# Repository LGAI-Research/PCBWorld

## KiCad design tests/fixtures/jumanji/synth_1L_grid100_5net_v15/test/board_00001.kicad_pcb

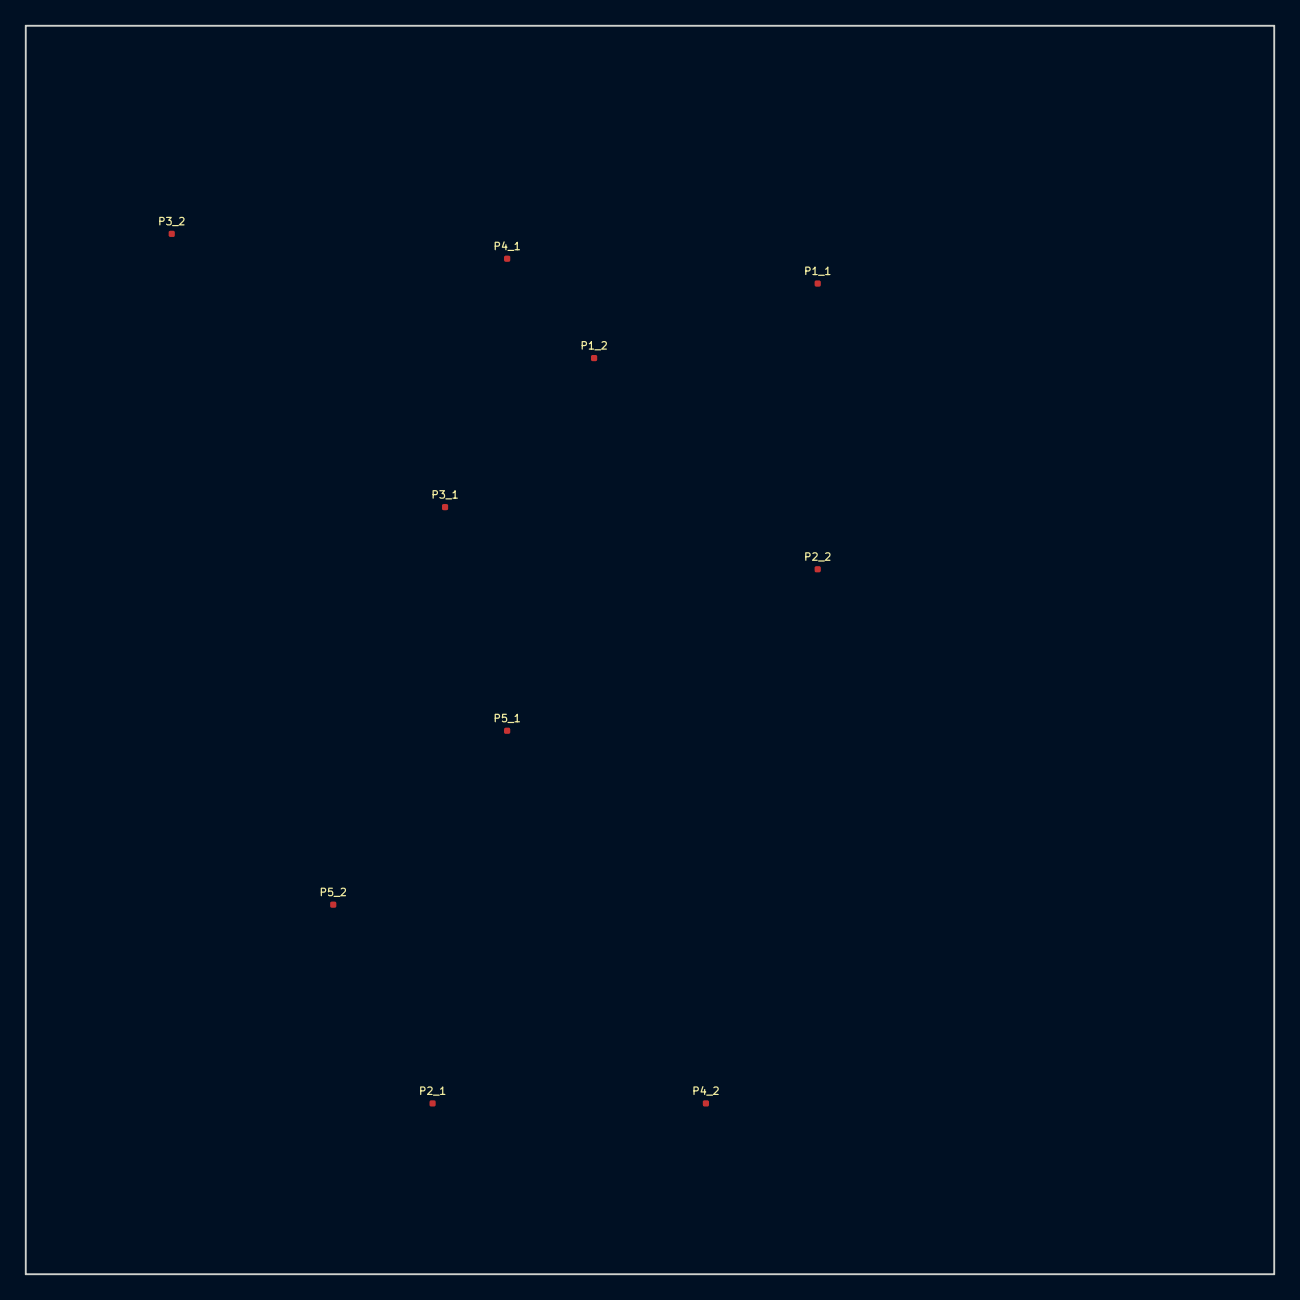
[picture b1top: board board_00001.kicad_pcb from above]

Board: 2 copper layers, 100.5 x 100.5 mm, 10 parts (0 on the bottom side), 5 nets, no tracks yet.

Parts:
P1_1, P2_1, P3_1, P4_1, P5_1: Pad1; FCu
P1_2, P2_2, P3_2, P4_2, P5_2: Pad2; FCu

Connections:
NET1: P1_1.1, P1_2.1
NET2: P2_1.1, P2_2.1
NET3: P3_1.1, P3_2.1
NET4: P4_1.1, P4_2.1
NET5: P5_1.1, P5_2.1

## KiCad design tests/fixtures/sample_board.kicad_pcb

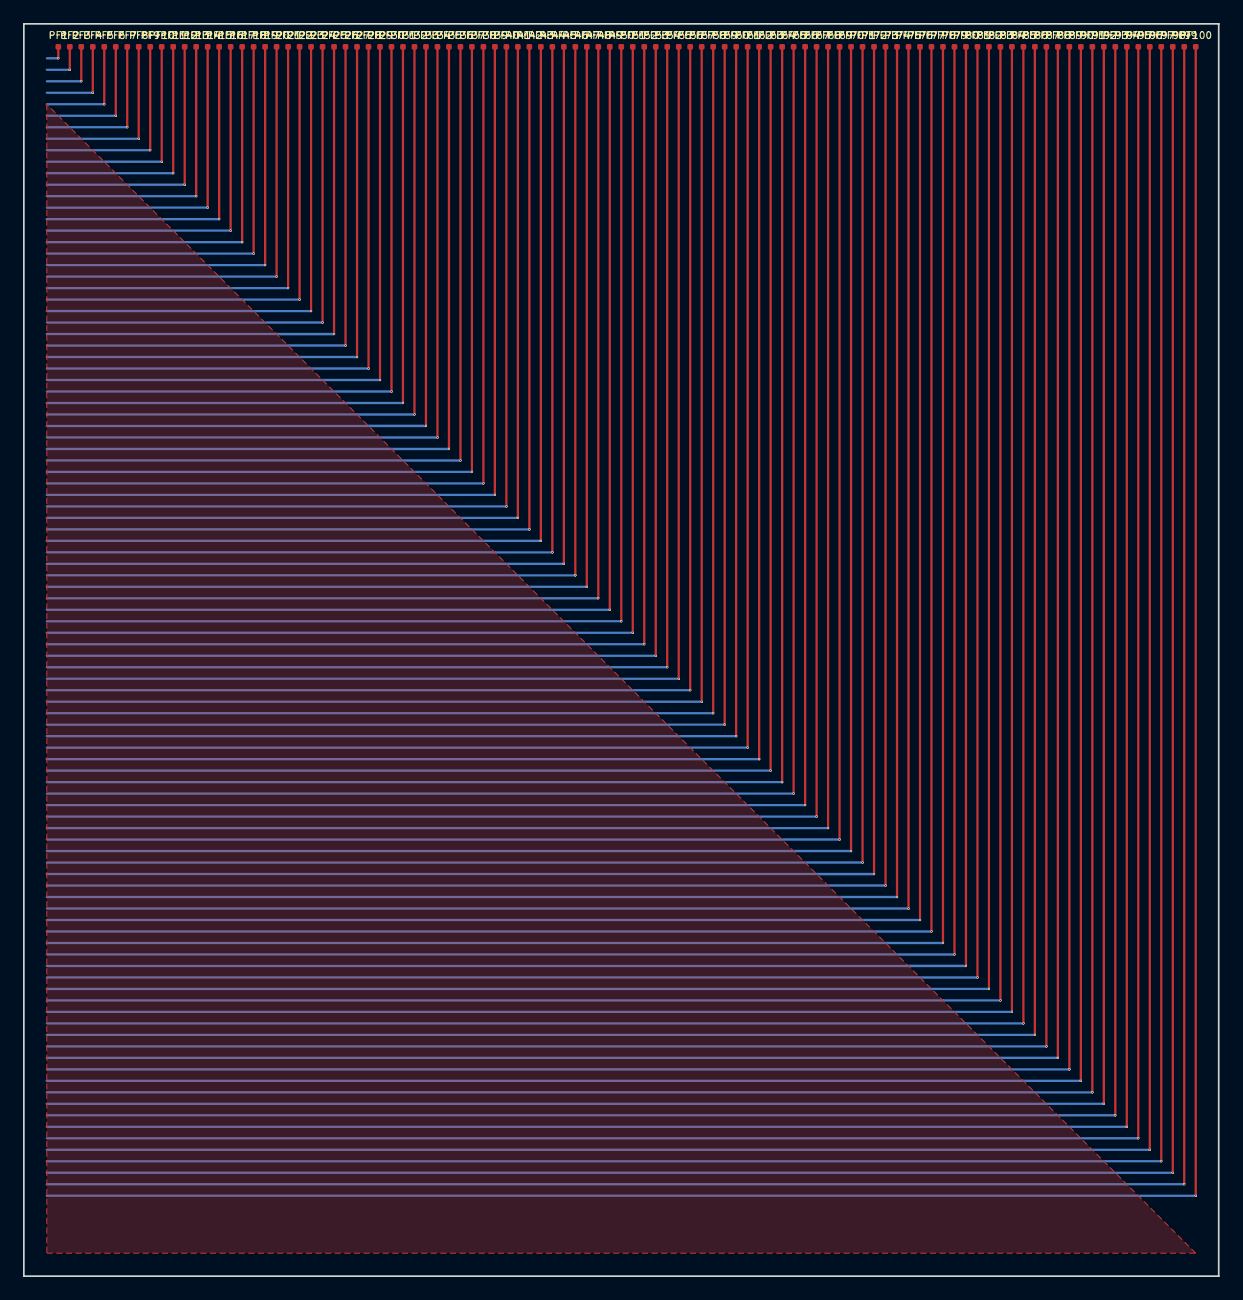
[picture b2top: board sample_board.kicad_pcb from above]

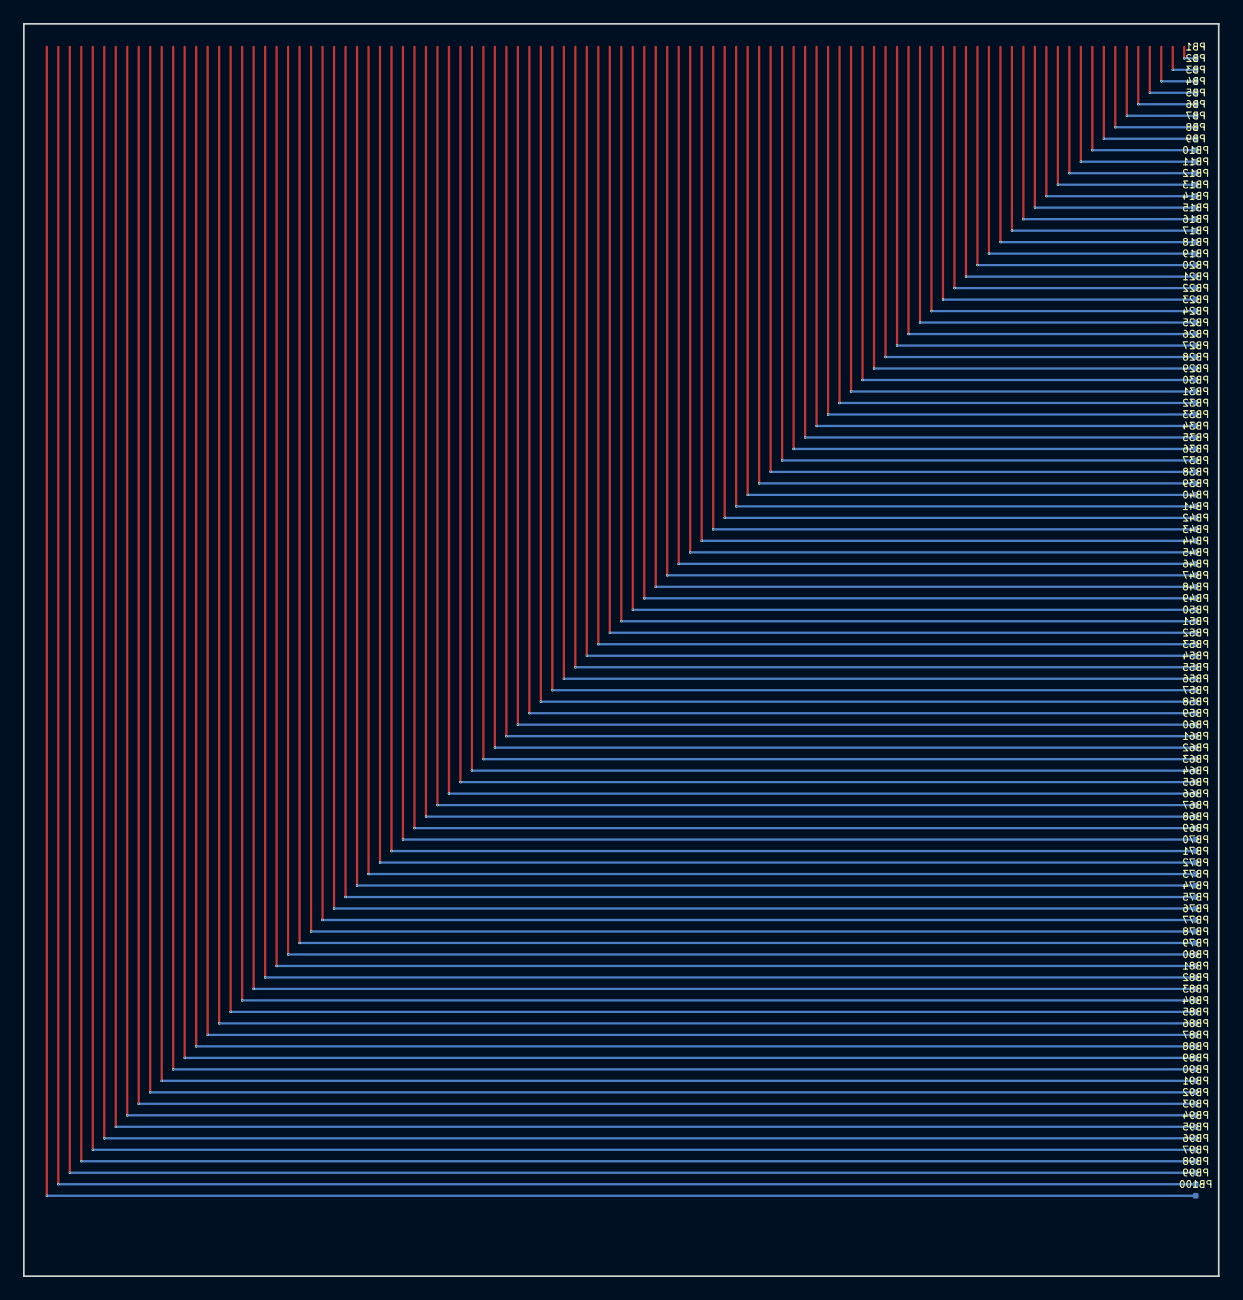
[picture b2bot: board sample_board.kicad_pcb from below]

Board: 2 copper layers, 104.0 x 109.0 mm, 200 parts (100 on the bottom side), 100 nets.

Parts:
PB1: Back1; Back
PB2: Back2; Back
PB3: Back3; Back
PB4: Back4; Back
PB5: Back5; Back
PB6: Back6; Back
PB7: Back7; Back
PB8: Back8; Back
PB9: Back9; Back
PB10: Back10; Back
PB11: Back11; Back
PB12: Back12; Back
PB13: Back13; Back
PB14: Back14; Back
PB15: Back15; Back
PB16: Back16; Back
PB17: Back17; Back
PB18: Back18; Back
PB19: Back19; Back
PB20: Back20; Back
PB21: Back21; Back
PB22: Back22; Back
PB23: Back23; Back
PB24: Back24; Back
PB25: Back25; Back
PB26: Back26; Back
PB27: Back27; Back
PB28: Back28; Back
PB29: Back29; Back
PB30: Back30; Back
PB31: Back31; Back
PB32: Back32; Back
PB33: Back33; Back
PB34: Back34; Back
PB35: Back35; Back
PB36: Back36; Back
PB37: Back37; Back
PB38: Back38; Back
PB39: Back39; Back
PB40: Back40; Back
PB41: Back41; Back
PB42: Back42; Back
PB43: Back43; Back
PB44: Back44; Back
PB45: Back45; Back
PB46: Back46; Back
PB47: Back47; Back
PB48: Back48; Back
PB49: Back49; Back
PB50: Back50; Back
PB51: Back51; Back
PB52: Back52; Back
PB53: Back53; Back
PB54: Back54; Back
PB55: Back55; Back
PB56: Back56; Back
PB57: Back57; Back
PB58: Back58; Back
PB59: Back59; Back
PB60: Back60; Back
PB61: Back61; Back
PB62: Back62; Back
PB63: Back63; Back
PB64: Back64; Back
PB65: Back65; Back
PB66: Back66; Back
PB67: Back67; Back
PB68: Back68; Back
PB69: Back69; Back
PB70: Back70; Back
PB71: Back71; Back
PB72: Back72; Back
PB73: Back73; Back
PB74: Back74; Back
PB75: Back75; Back
PB76: Back76; Back
PB77: Back77; Back
PB78: Back78; Back
PB79: Back79; Back
PB80: Back80; Back
PB81: Back81; Back
PB82: Back82; Back
PB83: Back83; Back
PB84: Back84; Back
PB85: Back85; Back
PB86: Back86; Back
PB87: Back87; Back
PB88: Back88; Back
PB89: Back89; Back
PB90: Back90; Back
PB91: Back91; Back
PB92: Back92; Back
PB93: Back93; Back
PB94: Back94; Back
PB95: Back95; Back
PB96: Back96; Back
PB97: Back97; Back
PB98: Back98; Back
PB99: Back99; Back
PB100: Back100; Back
PF1: Front1; Front
PF2: Front2; Front
PF3: Front3; Front
PF4: Front4; Front
PF5: Front5; Front
PF6: Front6; Front
PF7: Front7; Front
PF8: Front8; Front
PF9: Front9; Front
PF10: Front10; Front
PF11: Front11; Front
PF12: Front12; Front
PF13: Front13; Front
PF14: Front14; Front
PF15: Front15; Front
PF16: Front16; Front
PF17: Front17; Front
PF18: Front18; Front
PF19: Front19; Front
PF20: Front20; Front
PF21: Front21; Front
PF22: Front22; Front
PF23: Front23; Front
PF24: Front24; Front
PF25: Front25; Front
PF26: Front26; Front
PF27: Front27; Front
PF28: Front28; Front
PF29: Front29; Front
PF30: Front30; Front
PF31: Front31; Front
PF32: Front32; Front
PF33: Front33; Front
PF34: Front34; Front
PF35: Front35; Front
PF36: Front36; Front
PF37: Front37; Front
PF38: Front38; Front
PF39: Front39; Front
PF40: Front40; Front
PF41: Front41; Front
PF42: Front42; Front
PF43: Front43; Front
PF44: Front44; Front
PF45: Front45; Front
PF46: Front46; Front
PF47: Front47; Front
PF48: Front48; Front
PF49: Front49; Front
PF50: Front50; Front
PF51: Front51; Front
PF52: Front52; Front
PF53: Front53; Front
PF54: Front54; Front
PF55: Front55; Front
PF56: Front56; Front
PF57: Front57; Front
PF58: Front58; Front
PF59: Front59; Front
PF60: Front60; Front
PF61: Front61; Front
PF62: Front62; Front
PF63: Front63; Front
PF64: Front64; Front
PF65: Front65; Front
PF66: Front66; Front
PF67: Front67; Front
PF68: Front68; Front
PF69: Front69; Front
PF70: Front70; Front
PF71: Front71; Front
PF72: Front72; Front
PF73: Front73; Front
PF74: Front74; Front
PF75: Front75; Front
PF76: Front76; Front
PF77: Front77; Front
PF78: Front78; Front
PF79: Front79; Front
PF80: Front80; Front
PF81: Front81; Front
PF82: Front82; Front
PF83: Front83; Front
PF84: Front84; Front
PF85: Front85; Front
PF86: Front86; Front
PF87: Front87; Front
PF88: Front88; Front
PF89: Front89; Front
PF90: Front90; Front
PF91: Front91; Front
PF92: Front92; Front
PF93: Front93; Front
PF94: Front94; Front
PF95: Front95; Front
PF96: Front96; Front
PF97: Front97; Front
PF98: Front98; Front
PF99: Front99; Front
PF100: Front100; Front

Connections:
NET1: PB1.1, PF1.1
NET2: PB2.1, PF2.1
NET3: PB3.1, PF3.1
NET4: PB4.1, PF4.1
NET5: PB5.1, PF5.1
NET6: PB6.1, PF6.1
NET7: PB7.1, PF7.1
NET8: PB8.1, PF8.1
NET9: PB9.1, PF9.1
NET10: PB10.1, PF10.1
NET11: PB11.1, PF11.1
NET12: PB12.1, PF12.1
NET13: PB13.1, PF13.1
NET14: PB14.1, PF14.1
NET15: PB15.1, PF15.1
NET16: PB16.1, PF16.1
NET17: PB17.1, PF17.1
NET18: PB18.1, PF18.1
NET19: PB19.1, PF19.1
NET20: PB20.1, PF20.1
NET21: PB21.1, PF21.1
NET22: PB22.1, PF22.1
NET23: PB23.1, PF23.1
NET24: PB24.1, PF24.1
NET25: PB25.1, PF25.1
NET26: PB26.1, PF26.1
NET27: PB27.1, PF27.1
NET28: PB28.1, PF28.1
NET29: PB29.1, PF29.1
NET30: PB30.1, PF30.1
NET31: PB31.1, PF31.1
NET32: PB32.1, PF32.1
NET33: PB33.1, PF33.1
NET34: PB34.1, PF34.1
NET35: PB35.1, PF35.1
NET36: PB36.1, PF36.1
NET37: PB37.1, PF37.1
NET38: PB38.1, PF38.1
NET39: PB39.1, PF39.1
NET40: PB40.1, PF40.1
NET41: PB41.1, PF41.1
NET42: PB42.1, PF42.1
NET43: PB43.1, PF43.1
NET44: PB44.1, PF44.1
NET45: PB45.1, PF45.1
NET46: PB46.1, PF46.1
NET47: PB47.1, PF47.1
NET48: PB48.1, PF48.1
NET49: PB49.1, PF49.1
NET50: PB50.1, PF50.1
NET51: PB51.1, PF51.1
NET52: PB52.1, PF52.1
NET53: PB53.1, PF53.1
NET54: PB54.1, PF54.1
NET55: PB55.1, PF55.1
NET56: PB56.1, PF56.1
NET57: PB57.1, PF57.1
NET58: PB58.1, PF58.1
NET59: PB59.1, PF59.1
NET60: PB60.1, PF60.1
NET61: PB61.1, PF61.1
NET62: PB62.1, PF62.1
NET63: PB63.1, PF63.1
NET64: PB64.1, PF64.1
NET65: PB65.1, PF65.1
NET66: PB66.1, PF66.1
NET67: PB67.1, PF67.1
NET68: PB68.1, PF68.1
NET69: PB69.1, PF69.1
NET70: PB70.1, PF70.1
NET71: PB71.1, PF71.1
NET72: PB72.1, PF72.1
NET73: PB73.1, PF73.1
NET74: PB74.1, PF74.1
NET75: PB75.1, PF75.1
NET76: PB76.1, PF76.1
NET77: PB77.1, PF77.1
NET78: PB78.1, PF78.1
NET79: PB79.1, PF79.1
NET80: PB80.1, PF80.1
NET81: PB81.1, PF81.1
NET82: PB82.1, PF82.1
NET83: PB83.1, PF83.1
NET84: PB84.1, PF84.1
NET85: PB85.1, PF85.1
NET86: PB86.1, PF86.1
NET87: PB87.1, PF87.1
NET88: PB88.1, PF88.1
NET89: PB89.1, PF89.1
NET90: PB90.1, PF90.1
NET91: PB91.1, PF91.1
NET92: PB92.1, PF92.1
NET93: PB93.1, PF93.1
NET94: PB94.1, PF94.1
NET95: PB95.1, PF95.1
NET96: PB96.1, PF96.1
NET97: PB97.1, PF97.1
NET98: PB98.1, PF98.1
NET99: PB99.1, PF99.1
NET100: PB100.1, PF100.1

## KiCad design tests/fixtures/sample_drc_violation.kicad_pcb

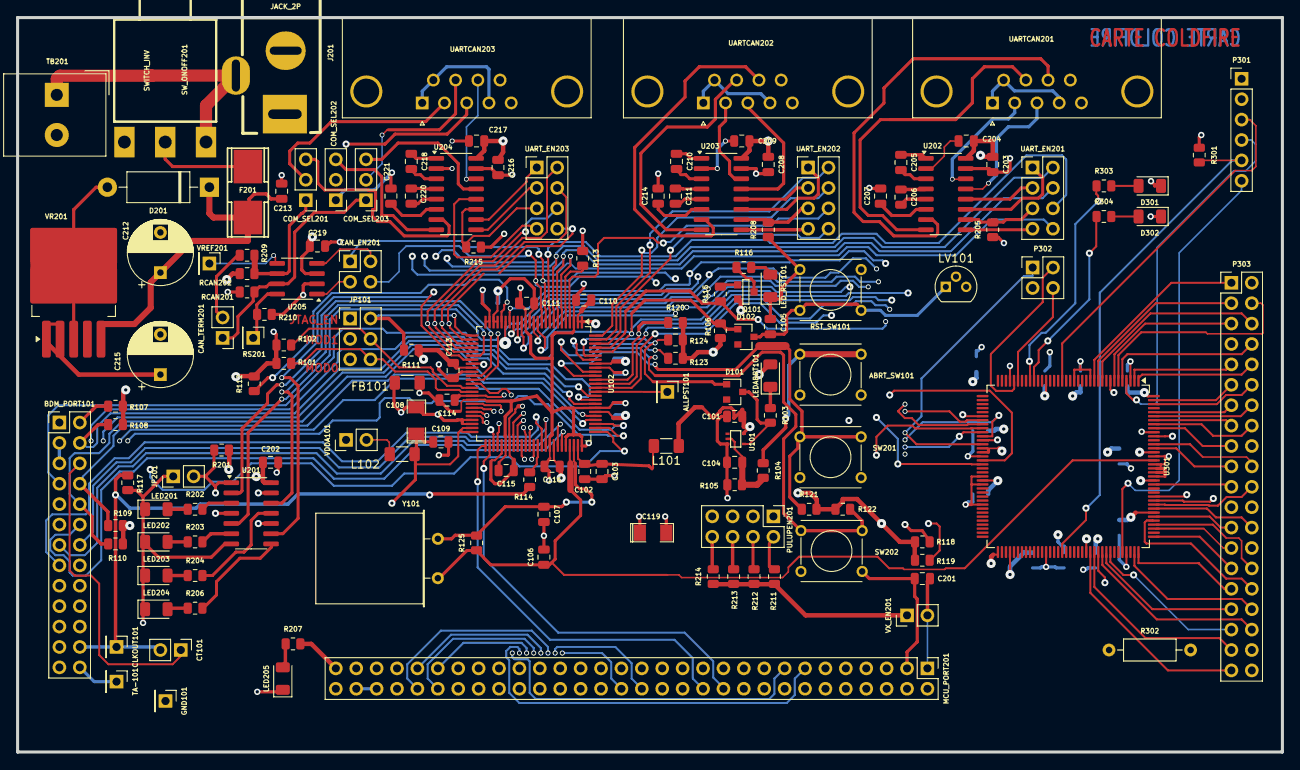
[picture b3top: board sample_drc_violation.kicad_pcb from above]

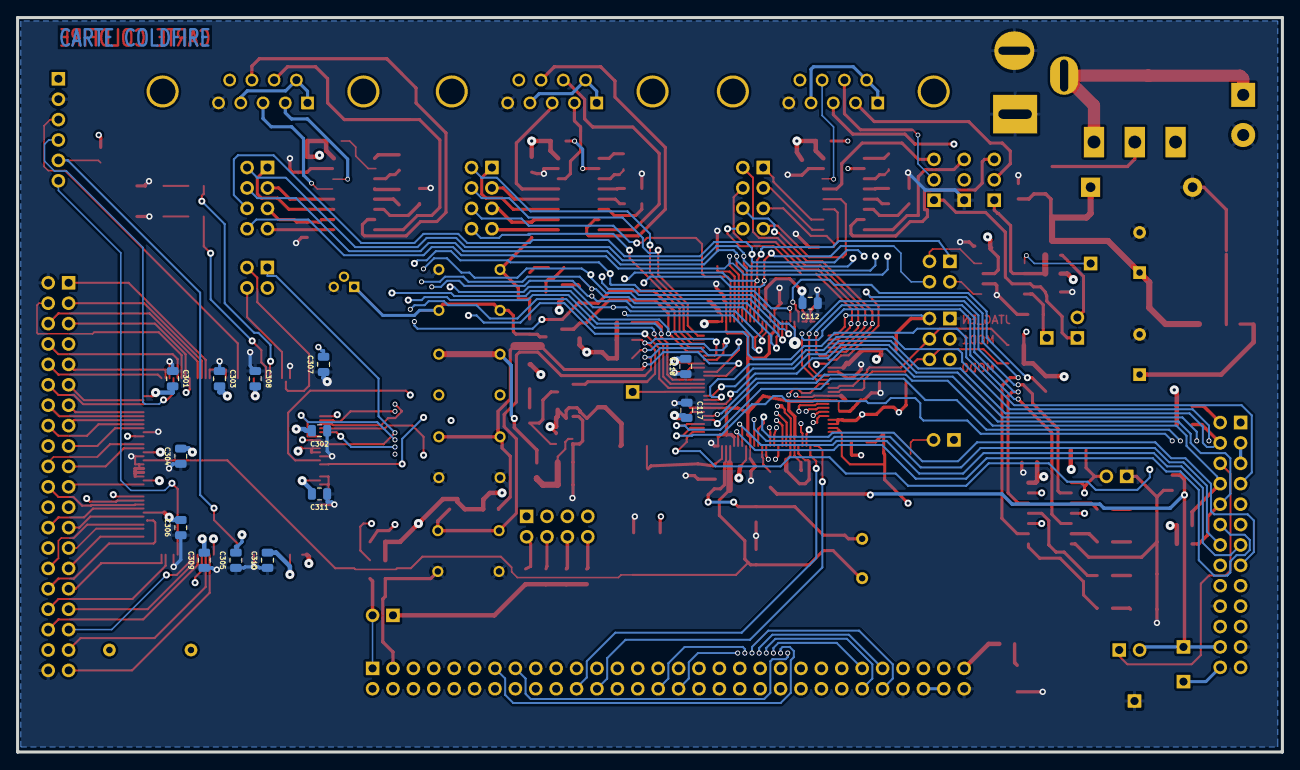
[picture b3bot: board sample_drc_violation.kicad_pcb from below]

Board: 4 copper layers, 157.5 x 91.4 mm, 160 parts (14 on the bottom side), 209 nets.

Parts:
ABRT_SW101: SW_PUSH; SW_PUSH_SMALL
ALLPST101: CONN_1; PinHeader_1x01_P2.54mm_Vertical
BDM_PORT101: CONN_13X2; PinHeader_2x13_P2.54mm_Vertical
C101, C103, C104, C109, C110, C111, C112, C113, C114, C115, C116, C117, C118, C201, C202, C203, C204, C205, C206, C207, C208, C209, C210, C211, C213, C214, C216, C217, C218, C219, C220, C221, C301, C302, C303, C304, C305, C306, C307, C308, C309, C310, C311: 100nF; C_0805_2012Metric
C102, C105: 1nF; C_0805_2012Metric
C106, C107: 10pF; C_0805_2012Metric
C108: 10uF; SM1206POL
C119: 100uF; SM1206POL
C212: 10uF; CP_Radial_D8.0mm_P5.00mm
C215: 220uF; CP_Radial_D8.0mm_P5.00mm
CAN_EN201: CONN_2X2; PinHeader_2x02_P2.54mm_Vertical
CAN_TERM201: JUMPER; PinHeader_1x02_P2.54mm_Vertical
CLKOUT101: CONN_1; PinHeader_1x01_P2.54mm_Vertical
COM_SEL201, COM_SEL202, COM_SEL203: CONN_3; PinHeader_1x03_P2.54mm_Vertical
CT101: JUMPER; PinHeader_1x02_P2.54mm_Vertical
D101, D102: BAT54; D_SOT-23_ANK
D201: 1N4004; D_DO-15_P12.70mm_Horizontal
D301, D302: LED; LED_1206_3216Metric
F201: FUSE; FSUPCMS
FB101: BEAD; R_1206_3216Metric_Pad1.30x1.75mm_HandSolder
GND101: CONN_1; PinHeader_1x01_P2.54mm_Vertical
J201: JACK_2P; JACK_ALIM
JP101: JUMPER_TRIPLE; PinHeader_2x03_P2.54mm_Vertical
JP201: JUMPER; PinHeader_1x02_P2.54mm_Vertical
L101, L102: 10uH; R_1206_3216Metric_Pad1.30x1.75mm_HandSolder
LED201, LED202, LED203, LED204, LED205: LED; LED_1206_3216Metric
LEDABRT101: LED_RED; LED_1206_3216Metric
LED_RST101: LED_RED; LED_1206_3216Metric
LV101: DS1818; TO-92
MCU_PORT201: CONN_30X2; PinHeader_2x30_P2.54mm_Vertical
P301: CONN_6; PinHeader_1x06_P2.54mm_Vertical
P302: CONN_2X2; PinHeader_2x02_P2.54mm_Vertical
P303: CONN_20X2; PinHeader_2x20_P2.54mm_Vertical
PULUPEN201: CONN_4X2; PinHeader_2x04_P2.54mm_Vertical
Q101: 3906; SOT23EBC
R101, R102, R106, R107, R108, R109, R110, R111, R112, R211, R212, R213, R214: 4,7K; R_0805_2012Metric
R103, R116, R202, R203, R204, R206, R207: 270; R_0805_2012Metric
R104, R210, R303, R304: 1K; R_0805_2012Metric
R105: 20K; R_0805_2012Metric
R113: 0; R_0805_2012Metric
R114: 22; R_0805_2012Metric
R115: 4.7K; R_0805_2012Metric
R117, R118, R119, R120, R121, R122, R123, R124, R201, R205, R208, R215: 10K; R_0805_2012Metric
R125: 1M; R_0805_2012Metric
R209: 62; R_0805_2012Metric
R301: 4K7; R_0805_2012Metric
R302: 3,3; R_Axial_DIN0207_L6.3mm_D2.5mm_P10.16mm_Horizontal
RCAN201, RCAN202: R; R_0805_2012Metric
RS201: CONN_1; PinHeader_1x01_P2.54mm_Vertical
RST_SW101: SW_PUSH; SW_PUSH_SMALL
SW201, SW202: SW_PUSH; SW_PUSH_SMALL
SW_ONOFF201: SWITCH_INV; SW_SPDT
TA-101: CONN_1; PinHeader_1x01_P2.54mm_Vertical
TB201: CONN_2; Altech_AK300_1x02_P5.00mm_45-Degree
U101: 74AHC1G14; SOT353
U102: MCF5213-LQFP100; LQFP-100_14x14mm_P0.5mm
U201: 74HC125; SOIC-14_3.9x8.7mm_P1.27mm
U202, U203, U204: MAX202; SOIC-16_3.9x9.9mm_P1.27mm
U205: PCA82C251; SOIC-8_3.9x4.9mm_P1.27mm
U301: XCR3256-TQ144; TQFP-144_20x20mm_P0.5mm
UARTCAN201, UARTCAN202, UARTCAN203: DB9; DSUB-9_Female_Horizontal_P2.77x2.84mm_EdgePinOffset7.70mm_H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
UART_EN201, UART_EN202, UART_EN203: CONN_4X2; PinHeader_2x04_P2.54mm_Vertical
VDDA101: JUMPER; PinHeader_1x02_P2.54mm_Vertical
VR201: LT1129_QPACK; TO-263-5_TabPin3
VREF201: CONN_1; PinHeader_1x01_P2.54mm_Vertical
VX_EN201: JUMPER; PinHeader_1x02_P2.54mm_Vertical
Y101: 8MHz; Crystal_HC18-U_Horizontal

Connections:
+3.3V: ABRT_SW101.2, BDM_PORT101.9, BDM_PORT101.25 (P24), C101.2, C110.1, C111.1, C112.1, C113.1, C114.1, C115.1, C116.1, C117.1, C118.1, C119.1, C202.1, C203.1, C204.1, C208.1, C209.1, C215.1, C216.1, C217.1, C219.1, C301.1, C302.1, C303.1, C304.1, C305.1, C306.1, C307.1, C308.1, C309.1, C310.1, C311.1, L101.1, LEDABRT101.2 (A), LV101.2 (In), MCU_PORT201.59, P301.1, Q101.1 (E), R101.1, R102.1, R106.1, R107.1, R108.1, R109.1, R110.1, R111.1, R112.2, R118.2, R119.2, R120.2, R121.2, R122.2, R123.2, R124.2, R201.1, R207.2, R211.1, R212.1, R213.1, R214.1, R301.1, R302.1, RCAN202.1, U101.5 (VCC), U102.1 (VCC), U102.2 (VCC), U102.14 (VCC), U102.22 (VCC), U102.23 (VCC), U102.34 (VCC), U102.41 (VCC), U102.55 (VSTBY), U102.57 (VCC), U102.68 (VCC), U102.81 (VCC), U102.93 (VCC), U201.14 (VCC), U202.16 (VCC), U203.16 (VCC), U204.16 (VCC), U205.3 (VCC), U301.24 (VCC), U301.50 (VCC), U301.51 (VCC), U301.58 (VCC), U301.73 (VCC), U301.76 (VCC), U301.95 (VCC), U301.115 (VCC), U301.123 (VCC), U301.130 (VCC), U301.144 (VCC), VDDA101.1, VR201.1 (OUT), VR201.2 (SENSE), VX_EN201.1
/ALLPST: ALLPST101.1, U102.86 (ALLPST)
/AN0: MCU_PORT201.10, U102.43 (AN0/PAN0)
/AN1: MCU_PORT201.12, U102.44 (AN1/PAN1)
/AN2: MCU_PORT201.14, U102.45 (AN2/PAN2)
/AN3: MCU_PORT201.16, U102.46 (AN3/PAN3)
/AN4: MCU_PORT201.18, U102.54 (AN4/PAN4)
/AN5: MCU_PORT201.20, U102.53 (AN5/PAN5)
/AN6: MCU_PORT201.22, U102.52 (AN6/PAN6)
/AN7: MCU_PORT201.24, U102.51 (AN7/PAN7)
/BKPT-: BDM_PORT101.2, R107.2, U102.76 (~BKPT/TMS)
/CANRX: CAN_EN201.4, MCU_PORT201.28, PULUPEN201.7, U102.11 (SDA/CANRX/PAS1/URXD2)
/CANTX: CAN_EN201.1, MCU_PORT201.26, PULUPEN201.5, U102.10 (SCL/CANTX/PAS0/UTXD2)
/CLKIN/EXTAL: C107.1, R125.2, U102.73 (CLKIN/EXTAL), Y101.1
/CLKMOD0: JP101.6, R101.2, U102.40 (CLKMOD0)
/CLKMOD1: JP101.4, R102.2, U102.39 (CLKMOD1)
/DDAT0: BDM_PORT101.19, U102.77 (DDATA0/PDD4)
/DDAT1: BDM_PORT101.18, U102.78 (DDATA1/PDD5)
/DDAT2: BDM_PORT101.17, U102.83 (DDATA2/PDD6)
/DDAT3: BDM_PORT101.16, U102.84 (DDATA3/PDD7)
/DSCLK: BDM_PORT101.4, R108.2, U102.85 (DSCLK/~TRST)
/DSI: BDM_PORT101.8, R109.2, U102.79 (DSI/TDI)
/DSO: BDM_PORT101.10, R110.2, U102.80 (DSO/TDO)
/DSPI_DOUT: MCU_PORT201.17, U102.17 (QSPI_DOUT/EZPQ/CANTX/RXD0/PQS0), U301.47 (M12)
/DTIN0: MCU_PORT201.34, U102.36 (DTIN0/DTOUT0/PWM0/PTC0), U201.2 (D)
/DTIN1: MCU_PORT201.36, U102.37 (DTIN1/DTOUT1/PWM2/PTC1), U201.5 (D)
/DTIN2: MCU_PORT201.38, U102.31 (DTIN2/DTOUT2/PWM4/PTC2), U201.12 (D)
/DTIN3: MCU_PORT201.40, U102.32 (DTIN3/DTOUT3/PWM6/PTC3), U201.9 (D)
/GPT0: MCU_PORT201.49, U102.58 (GPT0/PWM1/PTA0)
/GPT1: MCU_PORT201.50, U102.59 (GPT1/PWM3/PTA1)
/GPT2: MCU_PORT201.51, U102.61 (GPT2PWM5//PTA2)
/GPT3: MCU_PORT201.52, U102.62 (GPT3/PWM7/PTA3)
/IRQ-1: MCU_PORT201.2, R118.1, U102.87 (~IRQ1/PNQ1/SYNCA/PWM1), U301.42 (O2)
/IRQ-2: MCU_PORT201.8, R119.1, U102.88 (~IRQ2/PNQ2), U301.43 (O1)
/IRQ-3: MCU_PORT201.31, R120.1, U102.89 (~IRQ3/PNQ3), U301.44 (O0)
/IRQ-4: MCU_PORT201.33, R121.1, SW201.1, U102.90 (~IRQ4/PNQ4)
/IRQ-5: MCU_PORT201.35, R122.1, SW202.1, U102.91 (~IRQ5/PNQ5)
/IRQ-6: MCU_PORT201.37, R123.1, U102.94 (~IRQ6/PNQ6)
/IRQ-7: D101.2 (A), MCU_PORT201.39, R124.1, U102.95 (~IRQ7/PNQ7)
/JTAG_EN: JP101.2, R111.2, U102.26 (JTAG_EN)
/PST0: BDM_PORT101.15, U102.65 (PST0/PDD0)
/PST1: BDM_PORT101.14, U102.66 (PST1/PDD1)
/PST2: BDM_PORT101.13, U102.69 (PST2/PDD2)
/PST3: BDM_PORT101.12, U102.70 (PST3/PDD3)
/PWM1: MCU_PORT201.13, U102.38 (PWM1/PTD0)
/PWM3: MCU_PORT201.15, U102.33 (PWM3/PTD1)
/PWM5: MCU_PORT201.30, U102.60 (PWM5/PTD2)
/PWM7: MCU_PORT201.32, U102.63 (PWM7/PTD3)
/QSPI_CLK: MCU_PORT201.21, PULUPEN201.1, U102.18 (QSPI_CLK/EZPCK/SCL/RTS1/PQS2), U301.48 (M11)
/QSPI_CS0: MCU_PORT201.23, PULUPEN201.3, U102.20 (QSPI_CS0/SDA/CTS1/PQS3)
/QSPI_CS1: MCU_PORT201.25, U102.19 (QSPI_CS1/PQS4), U301.54 (M1)
/QSPI_CS2: MCU_PORT201.27, U102.13 (QSPI_CS2/PQS5), U301.45 (M15)
/QSPI_CS3: MCU_PORT201.29, U102.12 (QSPI_CS3/SYNCA/SYNCB/PQS6)
/QSPI_DIN: MCU_PORT201.19, U102.16 (QSPI_DIN/EZPD/CANRX/RXD1/PQS1), U301.46 (M13)
/RCON-: MCU_PORT201.53, R112.1, U102.21 (RCON/EZPCS)
/RSTI-: BDM_PORT101.7, D102.2 (A), MCU_PORT201.6, R106.2, U102.96 (RSTI)
/RSTO-: MCU_PORT201.4, R115.1, U102.97 (RSTO)
/TCLK: BDM_PORT101.24 (P20), CLKOUT101.1, CT101.2, R114.2, R117.1
/UCTS0: MCU_PORT201.44, U102.6 (~UCTS0/CANRX/PUA3), UART_EN201.8
/UCTS1: MCU_PORT201.11, P302.1, U102.98 (~UCTS1/SYNCA/URXD2/PUB3), U301.49 (M4), UART_EN202.8
/UCTS2: MCU_PORT201.48, U102.27 (~UCTS2/PUC3), UART_EN203.8
/URTS0: MCU_PORT201.42, U102.9 (~URTS0/CANTX/PUA2), UART_EN201.6
/URTS1: MCU_PORT201.9, P302.3, U102.4 (~URTS1/SYNCB/UTXD2/PUB2), U301.53 (M2), UART_EN202.6
/URTS2: MCU_PORT201.46, U102.30 (~URTS2/PUC2), UART_EN203.6
/URXD0: MCU_PORT201.43, U102.7 (URXD0/PUA1), UART_EN201.4
/URXD1: MCU_PORT201.7, U102.100 (URXD1/PUB1), UART_EN202.4
/URXD2: MCU_PORT201.47, U102.28 (URXD2/PUC1), UART_EN203.4
/UTXD0: MCU_PORT201.41, U102.8 (UTXD0/PUA0), UART_EN201.2
/UTXD1: MCU_PORT201.5, U102.99 (UTXD1/PUB0), UART_EN202.2
/UTXD2: MCU_PORT201.45, U102.29 (UTXD2/PUC0), UART_EN203.2
/VCCA: C108.1, C109.1, L102.2, MCU_PORT201.55, MCU_PORT201.57, U102.49 (VRH), U102.50 (VCCA)
/VDDPLL: C102.1, C103.1, L101.2, U102.74 (VCCPLL)
/XTAL: C106.1, R125.1, U102.72 (XTAL), U301.128 (CLK0/IN0), Y101.2
/inout_user/CAN_H: CAN_TERM201.1, COM_SEL203.1, RCAN201.2, U205.7 (CAN+)
/inout_user/CAN_L: COM_SEL201.1, R209.1, RCAN202.2, U205.6 (CAN-)
/inout_user/CTS0: U202.8 (R2IN), UARTCAN201.7
/inout_user/CTS1: U203.8 (R2IN), UARTCAN202.7
/inout_user/CTS2/CANH: COM_SEL203.2 (PM), UARTCAN203.7
/inout_user/RTS0: U202.7 (T2OUT), UARTCAN201.8
/inout_user/RTS1: U203.7 (T2OUT), UARTCAN202.8
/inout_user/RTS2: U204.14 (T1OUT), UARTCAN203.8
/inout_user/RXD0: U202.13 (R1IN), UARTCAN201.3
/inout_user/RXD1: U203.13 (R1IN), UARTCAN202.3
/inout_user/RXD2: COM_SEL202.2 (PM), UARTCAN203.3
/inout_user/RxD_CAN: CAN_EN201.2, U205.4 (RxD)
/inout_user/TXD0: U202.14 (T1OUT), UARTCAN201.2
/inout_user/TXD1: U203.14 (T1OUT), UARTCAN202.2
/inout_user/TXD2/CANL: COM_SEL201.2 (PM), UARTCAN203.2
/inout_user/TxD_CAN: CAN_EN201.3, U205.1 (TxD)
/xilinx/+3,3V_OUT: P303.38, R302.2
/xilinx/LED_TEST1: R303.1, U301.28 (N15)
/xilinx/LED_TEST2: R304.1, U301.27 (N14)
/xilinx/TCK: P301.5, R301.2, U301.89 (E0/TCK)
/xilinx/TDI: P301.4, U301.4 (J0/TDI)
/xilinx/TDO: P301.6, U301.104 (A2/TDO)
/xilinx/TMS: P301.3, U301.20 (N0/TMS)
/xilinx/XIL_D0: P303.1, U301.12 (L2)
/xilinx/XIL_D1: P303.3, U301.11 (J15)
/xilinx/XIL_D2: P303.5, U301.7 (J4)
/xilinx/XIL_D3: P303.7, U301.8 (J11)
/xilinx/XIL_D4: P303.9, U301.2 (I0)
/xilinx/XIL_D5: P303.11, U301.143 (I4)
/xilinx/XIL_D6: P303.13, U301.140 (I14)
/xilinx/XIL_D7: P303.15, U301.138 (K2)
/xilinx/XIL_D8: P303.17, U301.136 (K11)
/xilinx/XIL_D9: P303.19, U301.131 (K15)
/xilinx/XIL_D10: P303.21, U301.122 (D15)
/xilinx/XIL_D11: P303.23, U301.119 (D11)
/xilinx/XIL_D12: P303.25, U301.114 (D0)
/xilinx/XIL_D13: P303.27, U301.111 (B12)
/xilinx/XIL_D14: P303.29, U301.109 (B4)
/xilinx/XIL_D15: P303.31, U301.108 (B1)
/xilinx/XIL_D16: P303.33, U301.100 (A12)
/xilinx/XIL_D17: P303.35, U301.101 (A11)
/xilinx/XIL_D18: P303.37, U301.97 (C1)
/xilinx/XIL_D19: P303.39, U301.96 (C2)
/xilinx/XIL_D20: P303.4, U301.6 (J3)
/xilinx/XIL_D21: P303.6, U301.10 (J14)
/xilinx/XIL_D22: P303.8, U301.5 (J2)
/xilinx/XIL_D23: P303.10, U301.1 (I1)
/xilinx/XIL_D24: P303.12, U301.142 (I12)
/xilinx/XIL_D25: P303.14, U301.139 (I15)
/xilinx/XIL_D26: P303.16, U301.137 (K4)
/xilinx/XIL_D27: P303.18, U301.134 (K12)
/xilinx/XIL_D28: P303.20, U301.132 (K14)
/xilinx/XIL_D29: P303.22, U301.117 (D2)
/xilinx/XIL_D30: P303.24, U301.118 (D4)
/xilinx/XIL_D31: P303.26, U301.116 (D1)
/xilinx/XIL_D32: P303.28, U301.98 (C0)
/xilinx/XIL_D33: P303.30, U301.112 (B14)
/xilinx/XIL_D34: P303.32, U301.113 (B15)
/xilinx/XIL_D35: P303.34, U301.107 (B0)
/xilinx/XIL_D36: P303.36, U301.99 (A13)
GND: BDM_PORT101.3, BDM_PORT101.5, BDM_PORT101.11, BDM_PORT101.20, BDM_PORT101.23, C101.1, C102.2, C103.2, C104.2, C105.2, C106.2, C107.2, C110.2, C111.2, C112.2, C113.2, C114.2, C115.2, C116.2, C117.2, C118.2, C119.2, C201.1, C202.2, C203.2, C207.2, C208.2, C212.2, C213.2, C214.2, C215.2, C216.2, C219.2, C221.2, C301.2, C302.2, C303.2, C304.2, C305.2, C306.2, C307.2, C308.2, C309.2, C310.2, C311.2, COM_SEL202.1, D201.2 (A), D301.1 (K), D302.1 (K), FB101.1, GND101.1, J201.1, J201.2, JP101.1, JP101.3, JP101.5, JP201.1, LED201.1 (K), LED202.1 (K), LED203.1 (K), LED204.1 (K), LED205.1 (K), LED_RST101.1 (K), LV101.3 (Gbd), MCU_PORT201.3, MCU_PORT201.54, MCU_PORT201.60, P301.2, P303.2, P303.40, R105.2, R113.2, R117.2, R205.1, R208.1, R210.2, R215.1, RCAN201.1, RST_SW101.2, SW201.2, SW202.2, TB201.2 (PM), U101.3 (GND), U102.3 (GND), U102.15 (GND), U102.24 (GND), U102.25 (GND), U102.35 (GND), U102.42 (GND), U102.56 (GND), U102.67 (GND), U102.71 (GNDPLL), U102.75 (GND), U102.82 (GND), U102.92 (GND), U201.7 (GND), U202.15 (GND), U203.15 (GND), U204.15 (GND), U205.2 (GND), U301.3 (GND), U301.13 (PORT_EN), U301.17 (GND), U301.33 (GND), U301.52 (GND), U301.57 (GND), U301.59 (GND), U301.64 (GND), U301.85 (GND), U301.105 (GND), U301.124 (GND), U301.125 (CLK3/IN3), U301.126 (CLK2/IN2), U301.127 (CLK1/IN1), U301.129 (GND), U301.135 (GND), UARTCAN201.5, UARTCAN202.5, UARTCAN203.5, VR201.3 (GND)
GNDA: C108.2, C109.2, FB101.2, MCU_PORT201.56, MCU_PORT201.58, U102.47 (VSSA), U102.48 (VRL)
unnamed: ABRT_SW101.1, R104.1
unnamed: BDM_PORT101.6, CT101.1
unnamed: BDM_PORT101.26 (P22), TA-101.1
unnamed: C104.1, R104.2, R105.1, U101.2
unnamed: CAN_TERM201.2, R209.2
unnamed: COM_SEL201.3, U204.7 (T2OUT)
unnamed: COM_SEL202.3, U204.8 (R2IN)
unnamed: COM_SEL203.3, U204.13 (R1IN)
unnamed: D101.1 (K), R103.2, U101.4
unnamed: C105.1, D102.1 (K), LV101.1 (Rst), RST_SW101.1
unnamed: C212.1, C213.1, D201.1 (K), F201.2, VR201.5 (IN)
unnamed: D301.2 (A), R303.2
unnamed: D302.2 (A), R304.2
unnamed: F201.1, SW_ONOFF201.2
unnamed: L102.1, VDDA101.2
unnamed: LED201.2 (A), R202.1
unnamed: LED202.2 (A), R203.1
unnamed: LED203.2 (A), R204.1
unnamed: LED204.2 (A), R206.1
unnamed: LED205.2 (A), R207.1
unnamed: LEDABRT101.1 (K), R103.1
unnamed: LED_RST101.2 (A), R116.2
unnamed: C201.2, MCU_PORT201.1, VX_EN201.2
unnamed: PULUPEN201.2, R211.2
unnamed: PULUPEN201.4, R212.2
unnamed: PULUPEN201.6, R213.2
unnamed: PULUPEN201.8, R214.2
unnamed: Q101.2 (B), R115.2
unnamed: Q101.3 (C), R116.1
unnamed: J201.3, SW_ONOFF201.3, TB201.1
unnamed: R114.1, U102.64 (TCLK/PSTCLK/CLKOUT)
unnamed: R113.1, U102.5 (TEST)
unnamed: JP201.2, R201.2, U201.1 (E), U201.4 (E), U201.10 (E), U201.13 (E)
unnamed: R202.2, U201.3 (O)
unnamed: R203.2, U201.6 (O)
unnamed: R206.2, U201.8 (O)
unnamed: R204.2, U201.11 (O)
unnamed: C205.1, U202.1 (C1+)
unnamed: C205.2, U202.3 (C1-)
unnamed: C206.1, U202.4 (C2+)
unnamed: C206.2, U202.5 (C2-)
unnamed: U202.12 (R1OUT), UART_EN201.3
unnamed: U202.9 (R2OUT), UART_EN201.7
unnamed: U202.11 (T1IN), UART_EN201.1
unnamed: R205.2, U202.10 (T2IN), UART_EN201.5
unnamed: C204.2, U202.2 (V+)
unnamed: C207.1, U202.6 (V-)
unnamed: C210.1, U203.1 (C1+)
unnamed: C210.2, U203.3 (C1-)
unnamed: C211.1, U203.4 (C2+)
unnamed: C211.2, U203.5 (C2-)
unnamed: U203.12 (R1OUT), UART_EN202.3
unnamed: U203.9 (R2OUT), UART_EN202.7
unnamed: U203.11 (T1IN), UART_EN202.1
unnamed: R208.2, U203.10 (T2IN), UART_EN202.5
unnamed: C209.2, U203.2 (V+)
unnamed: C214.1, U203.6 (V-)
unnamed: C218.1, U204.1 (C1+)
unnamed: C218.2, U204.3 (C1-)
unnamed: C220.1, U204.4 (C2+)
unnamed: C220.2, U204.5 (C2-)
unnamed: U204.12 (R1OUT), UART_EN203.7
unnamed: U204.9 (R2OUT), UART_EN203.3
unnamed: R215.2, U204.11 (T1IN), UART_EN203.5
unnamed: U204.10 (T2IN), UART_EN203.1
unnamed: C217.2, U204.2 (V+)
unnamed: C221.1, U204.6 (V-)
unnamed: R210.1, RS201.1, U205.8 (Rsl)
unnamed: U205.5 (Vref), VREF201.1
unnamed: P302.4, U301.31 (P4)
unnamed: P302.2, U301.32 (P11)
unnamed: UARTCAN201.1, UARTCAN201.4, UARTCAN201.6
unnamed: UARTCAN202.1, UARTCAN202.4, UARTCAN202.6
unnamed: UARTCAN203.1, UARTCAN203.4, UARTCAN203.6

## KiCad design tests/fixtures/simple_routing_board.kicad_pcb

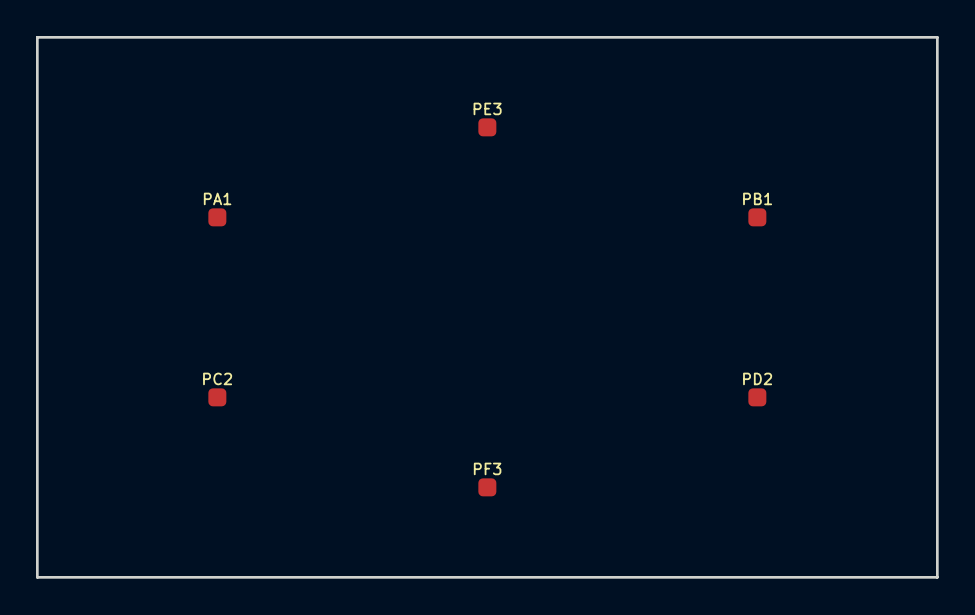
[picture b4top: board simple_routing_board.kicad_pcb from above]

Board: 2 copper layers, 50.0 x 30.0 mm, 6 parts (0 on the bottom side), 3 nets, no tracks yet.

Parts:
PA1: Pad1; FCu
PB1: Pad1; FCu
PC2: Pad2; FCu
PD2: Pad2; FCu
PE3: Pad3; FCu
PF3: Pad3; FCu

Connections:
NET1: PA1.1, PB1.1
NET2: PC2.1, PD2.1
NET3: PE3.1, PF3.1
